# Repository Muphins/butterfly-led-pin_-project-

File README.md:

# butterfly-led-pin Project
Butterfly shaped Hair-pin with RGB LEDs  

This project was born out of the desire to make something special for a gift.

It's a butterfly origami with LEDs stuck under the paper. An accelerometer and microcontroller allow animations that are driven by the head's movements when the pin is worn.  
It is battery powered. The initial goal was to have about 4 hours of autonomy. But with a battery I already had (100mAh) it lasts approximatly 1.5 hour. 
When no movement is detected it transitions itself into sleep mode and can last a little more than a month.

# Sources
All sources are available in this repo. The code is a submodule : https://github.com/Muphins/butterfly-led-pin-code-  

# WIP
## The PCB and its stencil

## Applying the paste

[Placing components (youtube)](https://www.youtube.com/watch?v=Wq-hjkRV1W0&list=PLRKnbB8N-SUT_lg6NkQAyX2fzEKrGeBuc&index=2)

## The LEDs
They are RGB addressable LEDs (neopixels).  
They measure 1.5x1.5mm  

First test to validate I can talk to one LED  
  
Second test with two LEDs and paper to test diffusion  

## Sleep mode
[Automaticaly engage sleep mode. Test current consumption (youtube)](https://www.youtube.com/watch?v=bKDfL658R1I&list=PLRKnbB8N-SUT_lg6NkQAyX2fzEKrGeBuc&index=3)  
[Test with battery (youtube)](https://www.youtube.com/watch?v=bKDfL658R1I&list=PLRKnbB8N-SUT_lg6NkQAyX2fzEKrGeBuc&index=3)  

## LEDs layout
Mapping the LEDs on the origami  

I drew the path for the wires and applied double sided tape  

And then placed the LEDs. Their pads are oriented to facilitate the wiring  

[Soldering a wire (youtube)](https://www.youtube.com/watch?v=1ZHcxBHy21E&list=PLRKnbB8N-SUT_lg6NkQAyX2fzEKrGeBuc&index=5)  
  
## Final assembly
[Test of all the LEDs before folding (youtube)](https://informotics.fr/images/articles/Papillon/12%20-%20cablage%20wip.jpg)  
During this test I noticed that the double sided tape diffuses the light, showing its shape through the paper:  

Before folding the origami I replaced the small squares by large patches of double sided tape.
  
[This video shows the butterfly folded and battery powered (youtube)](https://www.youtube.com/watch?v=GrwUBladvCI&list=PLRKnbB8N-SUT_lg6NkQAyX2fzEKrGeBuc&index=7)  
[This one shows one of the animations : Starlights (youtube)](https://www.youtube.com/watch?v=PvSEK_88dsE&list=PLRKnbB8N-SUT_lg6NkQAyX2fzEKrGeBuc&index=8)  
[Here the animation shows the accelerometer's X and Y axes (youtube)](https://www.youtube.com/watch?v=w01bJOyoW70&list=PLRKnbB8N-SUT_lg6NkQAyX2fzEKrGeBuc&index=9)

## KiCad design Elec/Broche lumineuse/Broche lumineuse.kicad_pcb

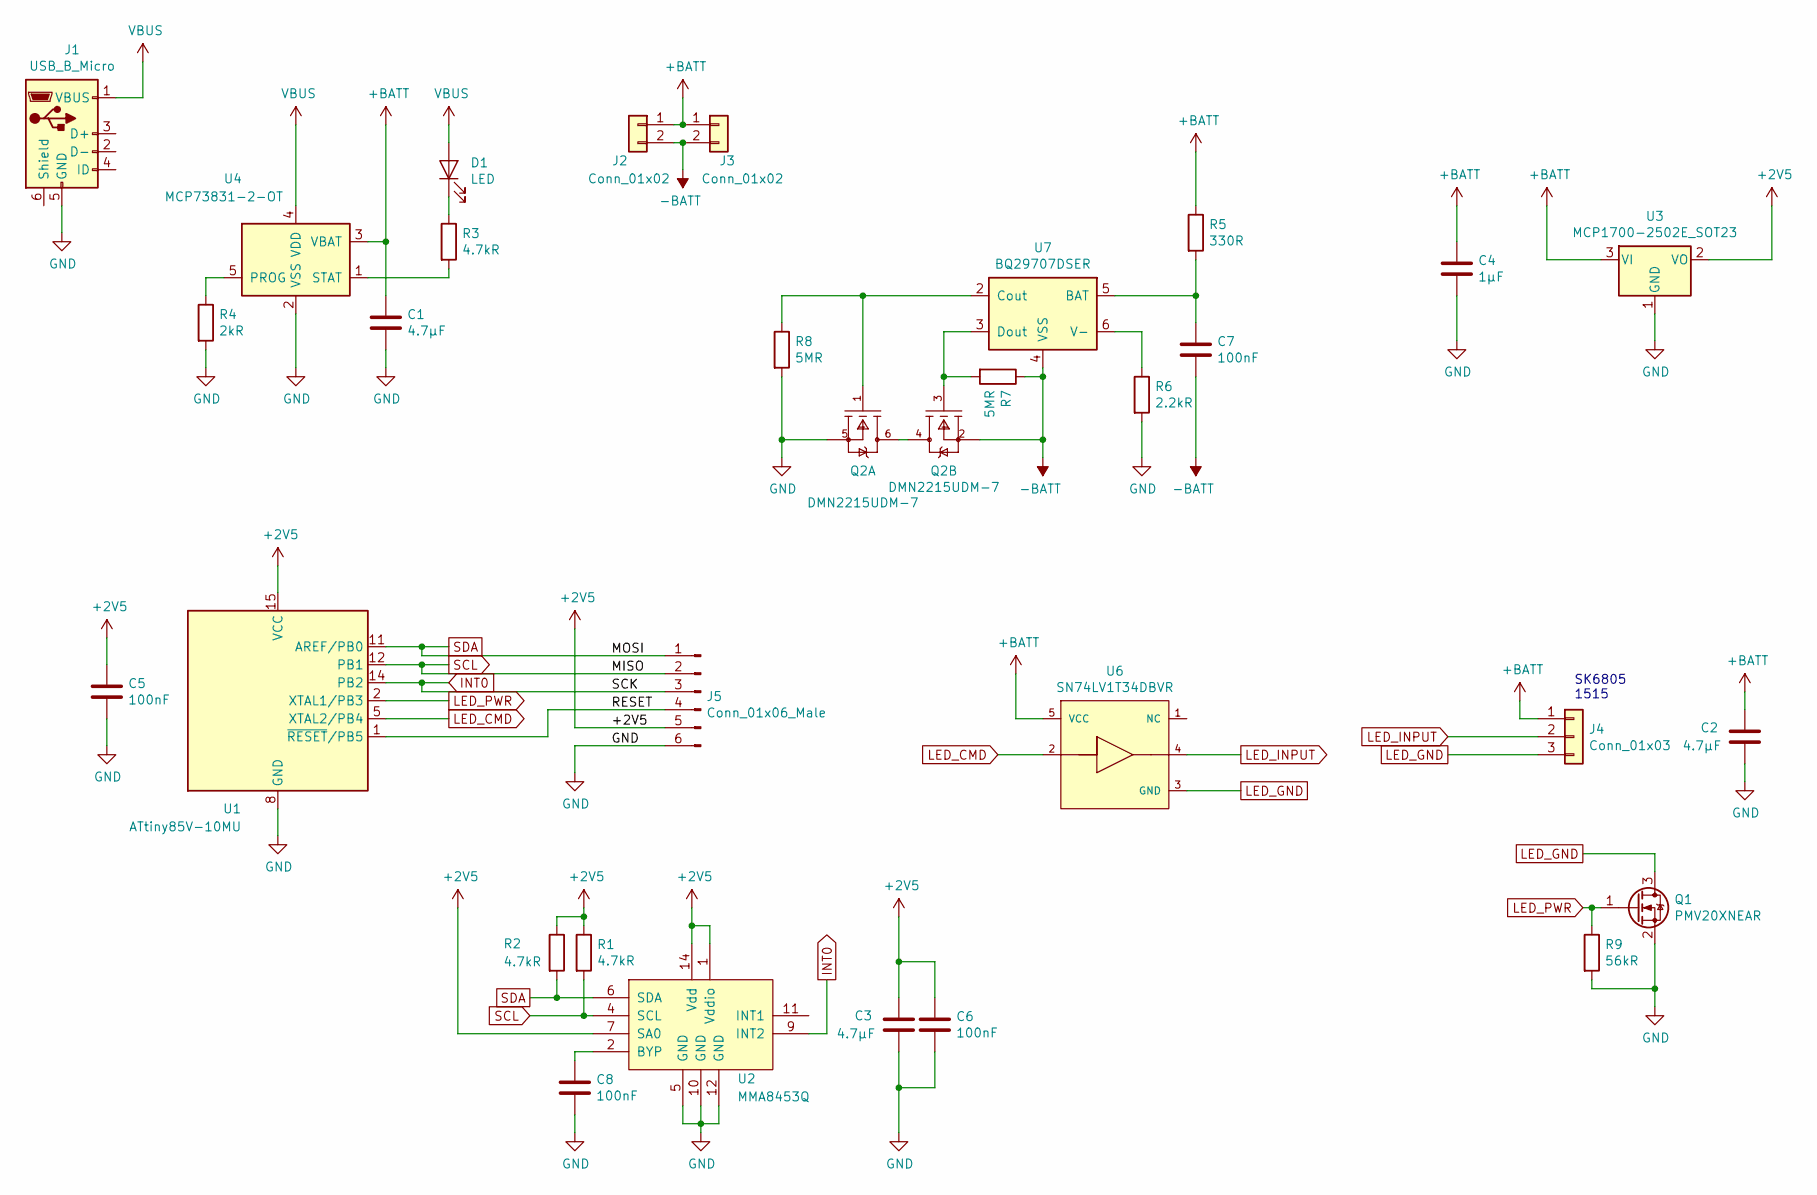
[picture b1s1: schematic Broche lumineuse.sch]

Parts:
C1, C2, C3: 4.7µF; C_0805_2012Metric
C4: 1µF; C_0402_1005Metric
C5, C6, C7, C8: 100nF; C_0402_1005Metric
D1: LED; D_0603_1608Metric
J1: USB_B_Micro; USB_Micro-AB_Molex_47590-0001
J2, J3: Conn_01x02; PinHeader_1x02_P1.27mm_Vertical
J4: Conn_01x03; PinHeader_1x03_P1.27mm_Vertical
J5: Conn_01x06_Male; JST_SH_SM06B-SRSS-TB_1x06-1MP_P1.00mm_Horizontal
Q1: PMV20XNEAR; SOT-23
Q2: DMN2215UDM-7; SOT-23-6; mouser part number 621-DMN2215UDM-7; digikey description MOSFET 2N-CH 20V 2A SOT-26
R1, R2, R3: 4.7kR; R_0402_1005Metric
R4: 2kR; R_0402_1005Metric
R5: 330R; R_0402_1005Metric
R6: 2.2kR; R_0402_1005Metric
R7, R8: 5MR; R_0402_1005Metric
R9: 56kR; R_0402_1005Metric
U1: ATtiny85V-10MU; QFN-20-1EP_4x4mm_P0.5mm_EP2.6x2.6mm
U2: MMA8453Q; NXP-SOT1676-1-01_2016-B-0
U3: MCP1700-2502E_SOT23; SOT-23
U4: MCP73831-2-OT; SOT-23-5
U6: SN74LV1T34DBVR; SOT-353_SC-70-5; mouser part number 595-SN74LV1T34DBVR; digikey description IC BUF NON-INVERT 5.5V SOT23-5
U7: BQ29707DSER; WSON-6_1.5x1.5mm_P0.5mm

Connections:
+2V5: C3.1, C5.1, C6.1, J5.5, R1.1, R2.1, U1.15 (VCC), U2.1 (Vddio), U2.7 (SA0), U2.14 (Vdd), U3.2 (VO)
+BATT: C1.1, C2.1, C4.1, J2.1, J3.1, J4.1, R5.1, U3.3 (VI), U4.3 (VBAT), U6.5 (VCC)
-BATT: C7.2, J2.2, J3.2, Q2.2 (S2), R7.1, U7.4 (VSS)
/RESET: J5.4, U1.1 (~RESET~/PB5)
GND: C1.2, C2.2, C3.2, C4.2, C5.2, C6.2, C8.2, J1.5 (GND), J5.6, Q1.2 (S), Q2.5 (S1), R4.2, R6.2, R8.2, R9.2, U1.8 (GND), U1.21 (GND), U2.5 (GND), U2.10 (GND), U2.12 (GND), U3.1 (GND), U4.2 (VSS)
INT0: J5.3, U1.14 (PB2), U2.9 (INT2)
LED_CMD: U1.5 (XTAL2/PB4), U6.2 (A)
LED_GND: J4.3, Q1.3 (D), U6.3 (GND)
LED_INPUT: J4.2, U6.4 (Y)
LED_PWR: Q1.1 (G), R9.1, U1.2 (XTAL1/PB3)
unnamed: C7.1, R5.2, U7.5 (BAT)
unnamed: C8.1, U2.2 (BYP)
unnamed: D1.1 (K), R3.1
unnamed: Q2.1 (G1), R8.1, U7.2 (Cout)
unnamed: Q2.3 (G2), R7.2, U7.3 (Dout)
unnamed: Q2.4 (D2), Q2.6 (D1)
unnamed: R3.2, U4.1 (STAT)
unnamed: R4.1, U4.5 (PROG)
unnamed: R6.1, U7.6 (V-)
SCL: J5.2, R1.2, U1.12 (PB1), U2.4 (SCL)
SDA: J5.1, R2.2, U1.11 (AREF/PB0), U2.6 (SDA)
VBUS: D1.2 (A), J1.1 (VBUS), U4.4 (VDD)

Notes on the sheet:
SK6805 1515

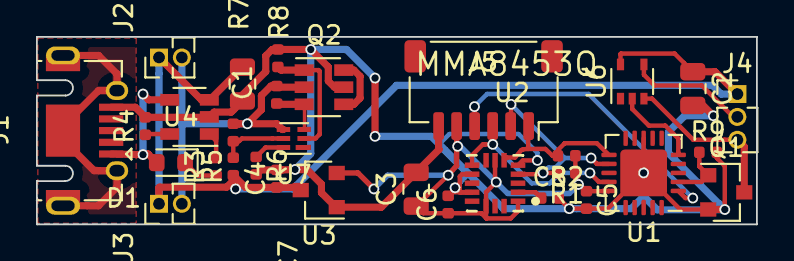
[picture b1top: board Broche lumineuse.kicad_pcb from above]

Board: 2 copper layers, 40.0 x 10.4 mm, 31 parts (0 on the bottom side), 22 nets.

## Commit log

2021-11-02 rev.1 hardware
2021-11-02 Maj schéma suivant tests sur rev.1; Maj temporaire du PCB
2021-11-02 Test de filtre passe-bas à base de moyenne
2021-11-02 Source adafruit neopixel
2021-11-02 Ajout submodule sources c++
2021-11-03 README.md
